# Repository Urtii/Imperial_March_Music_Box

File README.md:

# Imperial_March_Music_Box
Electronic music box Playing Imperial March with a rotating lego Star Wars Figure. Made by using Arduino Nano, piezo buzzer and DC motor.
Music code retrieved from https://www.instructables.com/id/How-to-easily-play-music-with-buzzer-on-arduino-Th/ made by eserra

Arduino code and EAGLE Schematics provided.

Project video is [HERE](https://youtu.be/Dg5EEnFGQ8I).

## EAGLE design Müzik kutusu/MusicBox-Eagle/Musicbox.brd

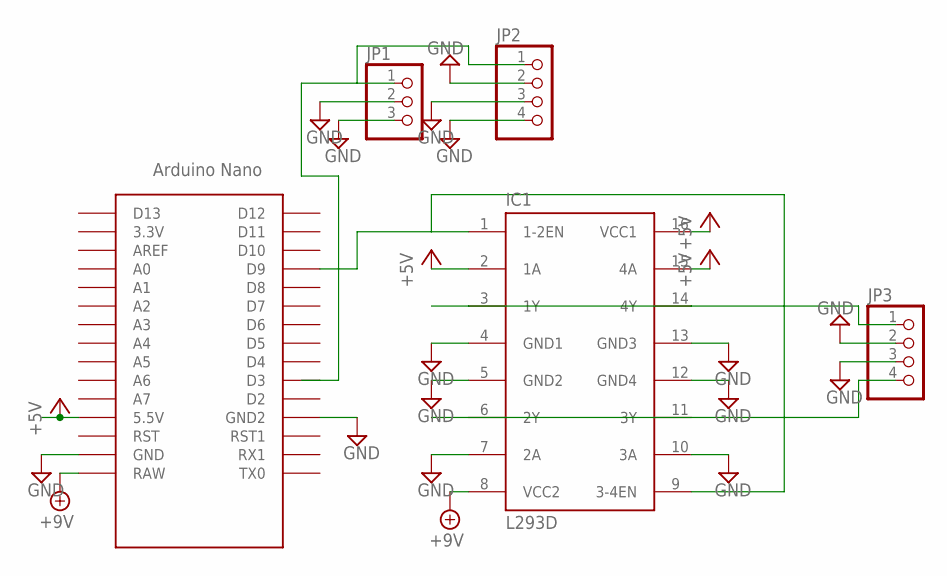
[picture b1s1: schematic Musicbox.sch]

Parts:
IC1: L293D; DIL16
JP1: PINHD-1X3; 1X03
JP2, JP3: PINHD-1X4; 1X04
U$1: NANO

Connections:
3Y: IC1.6 (2Y), IC1.11 (3Y), JP3.4
4Y: IC1.3 (1Y), IC1.14 (4Y), JP3.1
+5V: IC1.2 (1A), IC1.15 (4A), IC1.16 (VCC1), U$1.5V (5.5V)
+9V: IC1.8 (VCC2), U$1.RAW
BUZZER: JP1.1, JP2.1, U$1.D3
EN: IC1.1 (1-2EN), IC1.9 (3-4EN), U$1.D9
GND: IC1.4 (GND1), IC1.5 (GND2), IC1.7 (2A), IC1.10 (3A), IC1.12 (GND4), IC1.13 (GND3), JP1.2, JP1.3, JP2.2, JP2.3, JP2.4, JP3.2, JP3.3, U$1.GND, U$1.GND1 (GND2)

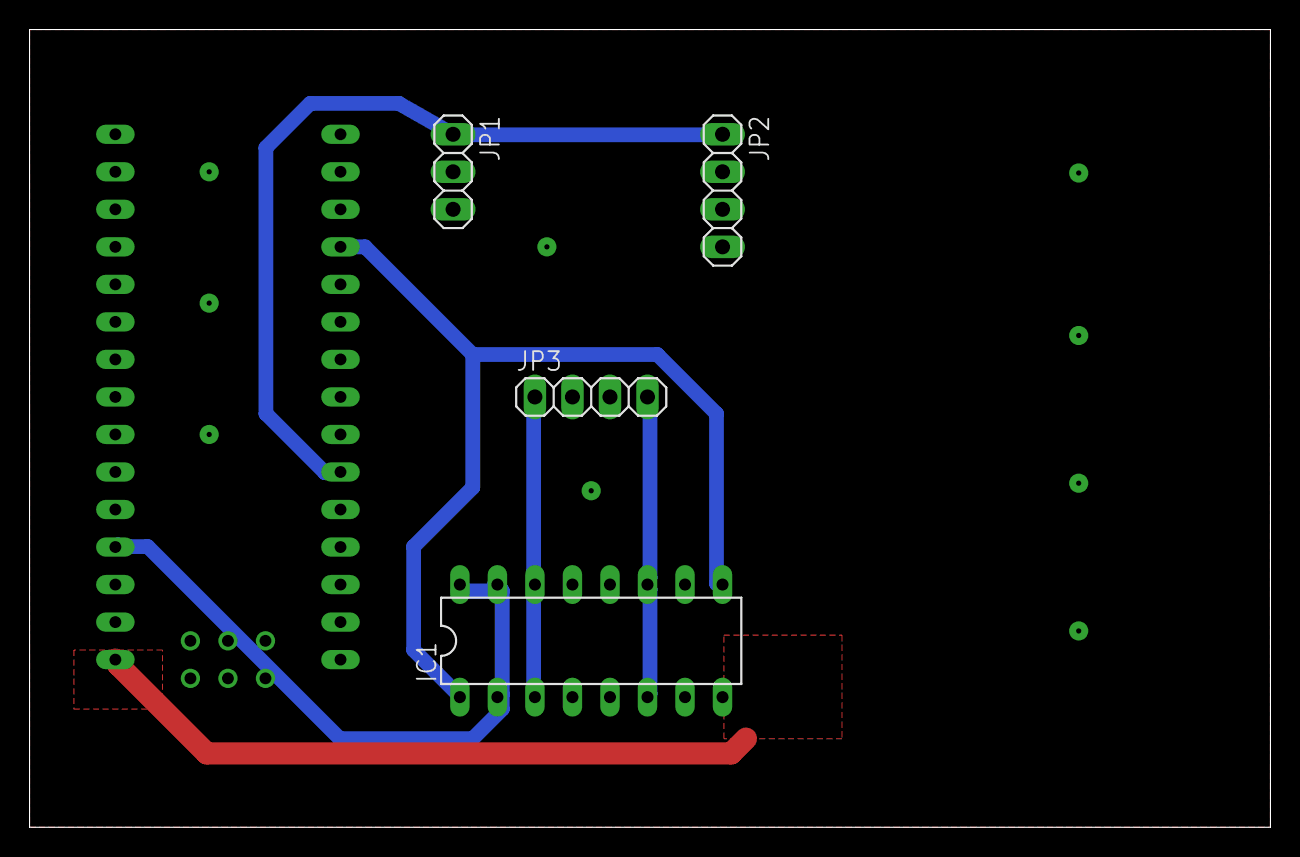
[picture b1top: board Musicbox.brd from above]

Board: 2 copper layers, 84.0 x 54.0 mm, 5 parts (0 on the bottom side), 7 nets.

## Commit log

2019-02-05 Final upload
